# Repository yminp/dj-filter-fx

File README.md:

# dj-filter-fx
A voltage-controlled DJ filter unit with LFO-like envelope function

## Disclaimer
This design has not yet been validated with a physical prototype. The schematic has been reviewed and analyzed, but practical issues may still be discovered during assembly and testing. A prototype is planned to be built and tested soon.

Anyone building the current revision should treat it as an experimental, pre-prototype design rather than a fully validated production circuit.

## Description
This project is a standalone analog filter effects unit intended primarily for DJ use.

The motivation came from the relative lack of dedicated standalone filter FX units for DJs. Filter effects are built into most modern DJ mixers, but older analog mixers may not provide an integrated filter effect. In those cases, applying a filter generally requires an external effects processor connected through the mixer's send/return path. The goal of this project is therefore to provide a dedicated external filter effect that can be used with such mixers while retaining an analog signal path.

Another major purpose of the project was educational. I wanted to explore the use of operational transconductance amplifiers (OTAs), particularly the LM13700, as voltage-controlled amplifiers (VCAs). In this design, VCAs are used inside a state-variable filter to provide voltage control of both the filter's center frequency and resonance Q. This required treating the OTA not merely as a conventional variable-resistance element, but as a controllable transconductance stage whose gain can be incorporated into the state-variable filter equations.

The project consequently combines several topics that I wanted to study in a practical audio circuit:

- voltage-controlled state-variable filters;
- LM13700 OTA/VCA design;
- voltage control of cutoff frequency and resonance;
- envelope-controlled filtering;
- LFO-based filter modulation;
- analog switching and filter-mode selection;
- balanced audio input and output interfacing;
- gain structure and headroom for professional/DJ audio levels (accepting input up to +26dBu, balanced).

The design is intended both as a usable DJ effects unit and as an experimental platform for learning analog filter and voltage-controlled amplifier design.

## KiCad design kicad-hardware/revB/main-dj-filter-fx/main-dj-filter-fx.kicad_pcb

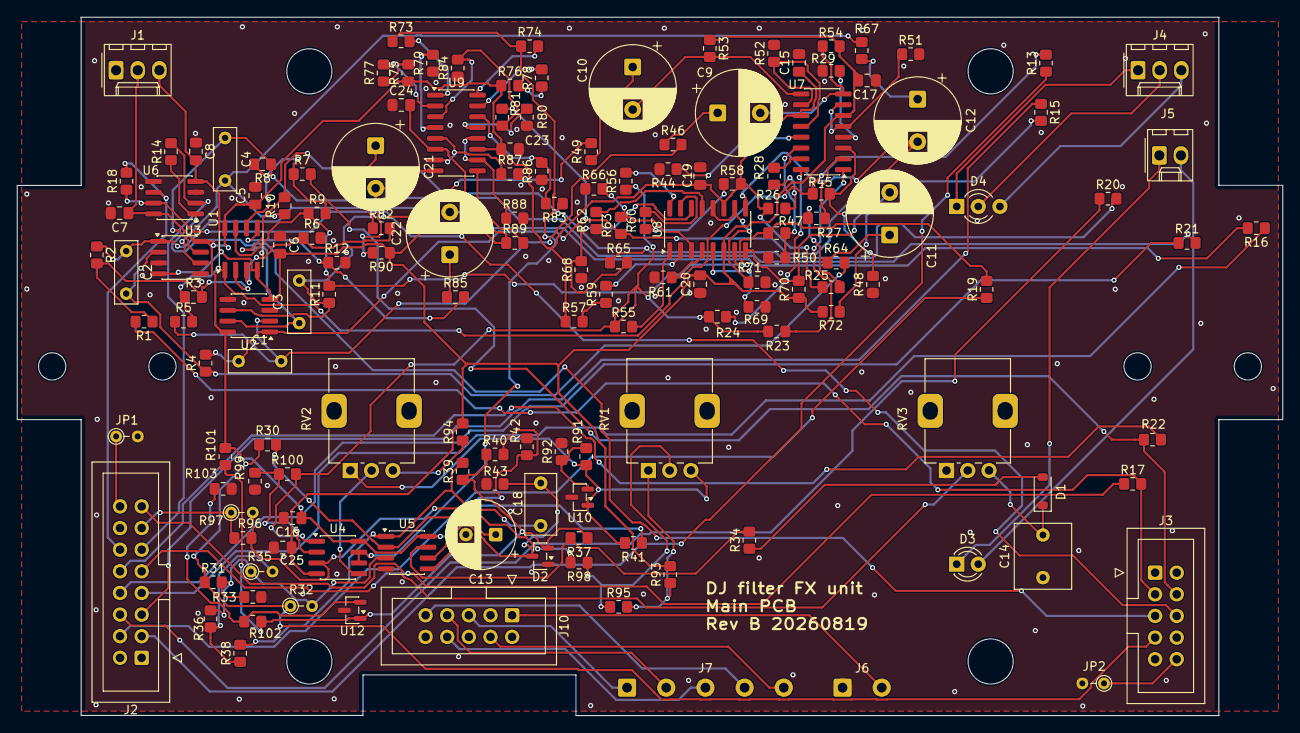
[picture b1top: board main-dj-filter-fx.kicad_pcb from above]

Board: 2 copper layers, 148.6 x 82.0 mm, 156 parts (0 on the bottom side), 116 nets.

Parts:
C1, C2, C3, C4: 2.2n, 1%; C_Rect_L7.2mm_W2.5mm_P5.00mm
C5, C6, C7, C8, C15, C16, C17, C19, C20, C23, C24, C25: 100n; C_0805_2012Metric_Pad1.18x1.45mm_HandSolder
C9, C10, C11, C12, C21, C22: 22u, NP; CP_Radial_D10.0mm_P5.00mm
C13: 10u, NP; CP_Radial_D8.0mm_P3.50mm
C14: 1u, film; C_Rect_L7.5mm_W6.5mm_P5.00mm
C18: 100n, film; C_Rect_L7.0mm_W3.5mm_P5.00mm
D1: MMSD4148; D_SOD-123
D2: BAT54S; SOT-23
D3: RED; LED_D3.0mm
D4: RED_GREEN; LED_D3.0mm-3
J1: PW_CONN; Molex_KK-254_AE-6410-03A_1x03_P2.54mm_Vertical
J2: SW_CONN; IDC-Header_2x08_P2.54mm_Vertical
J3: CONN_SIG; IDC-Header_2x05_P2.54mm_Vertical
J4: LED2color_CONN; Molex_KK-254_AE-6410-03A_1x03_P2.54mm_Vertical
J5: LED; Molex_KK-254_AE-6410-02A_1x02_P2.54mm_Vertical
J6: Conn_01x02_Socket; SolderWire-0.5sqmm_1x02_P4.6mm_D0.9mm_OD2.1mm
J7: Conn_01x05_Socket; SolderWire-0.5sqmm_1x05_P4.6mm_D0.9mm_OD2.1mm
J10: PHYSW_CONN; IDC-Header_2x05_P2.54mm_Vertical
JP1, JP2: Jumper_2_Small_Open; R_Axial_DIN0204_L3.6mm_D1.6mm_P2.54mm_Vertical
R1, R2, R3, R7, R8, R9, R37, R39, R53, R54, R70, R72, R89, R90: 4K7; R_0805_2012Metric_Pad1.20x1.40mm_HandSolder
R4, R5, R10, R11: 22M; R_0805_2012Metric_Pad1.20x1.40mm_HandSolder
R6, R12, R13, R14, R15, R16, R17, R18, R19, R20, R21, R22, R42, R102, R103: 10K; R_0805_2012Metric_Pad1.20x1.40mm_HandSolder
R23, R24, R55, R56, R73, R74: 27K; R_0805_2012Metric_Pad1.20x1.40mm_HandSolder
R25, R26, R46, R49, R57, R58, R64, R67, R75, R76, R92, R101: 2K2; R_0805_2012Metric_Pad1.20x1.40mm_HandSolder
R27, R28, R59, R60, R77, R78: 12K; R_0805_2012Metric_Pad1.20x1.40mm_HandSolder
R29, R44, R48, R50, R61, R62, R66, R68, R79, R80, R84, R86: 470; R_0805_2012Metric_Pad1.20x1.40mm_HandSolder
R30, R98: 220K; R_0805_2012Metric_Pad1.20x1.40mm_HandSolder
R31: 47K; R_0805_2012Metric_Pad1.20x1.40mm_HandSolder
R32: 100K, TH; R_Axial_DIN0204_L3.6mm_D1.6mm_P2.54mm_Vertical
R33, R99: 100K; R_0805_2012Metric_Pad1.20x1.40mm_HandSolder
R34: 1K; R_0805_2012Metric_Pad1.20x1.40mm_HandSolder
R35: 1M, TH; R_Axial_DIN0204_L3.6mm_D1.6mm_P2.54mm_Vertical
R36: 10R; R_0805_2012Metric_Pad1.20x1.40mm_HandSolder
R38: 1M; R_0805_2012Metric_Pad1.20x1.40mm_HandSolder
R40, R51, R52, R69, R71: 39K; R_0805_2012Metric_Pad1.20x1.40mm_HandSolder
R41: 680R; R_0805_2012Metric_Pad1.20x1.40mm_HandSolder
R43, R87, R88, R100: 68K; R_0805_2012Metric_Pad1.20x1.40mm_HandSolder
R45, R47, R63, R65, R81, R83: 150K; R_0805_2012Metric_Pad1.20x1.40mm_HandSolder
R82, R85: 3K3; R_0805_2012Metric_Pad1.20x1.40mm_HandSolder
R91: 8K2; R_0805_2012Metric_Pad1.20x1.40mm_HandSolder
R93: 5K6; R_0805_2012Metric_Pad1.20x1.40mm_HandSolder
R94: 18K; R_0805_2012Metric_Pad1.20x1.40mm_HandSolder
R95: 33K; R_0805_2012Metric_Pad1.20x1.40mm_HandSolder
R96: 330K; R_0805_2012Metric_Pad1.20x1.40mm_HandSolder
R97: 680K, TH; R_Axial_DIN0204_L3.6mm_D1.6mm_P2.54mm_Vertical
RV1, RV2, RV3: 100KA; Potentiometer_Alps_RK09K_Single_Vertical
U1, U6: RC4580; SOIC-8_3.9x4.9mm_P1.27mm
U2, U3: TL072; SOIC-8_3.9x4.9mm_P1.27mm
U4: LM358; SOIC-8_3.9x4.9mm_P1.27mm
U5: LM2903; SOIC-8_3.9x4.9mm_P1.27mm
U7, U8, U9: LM13700; SOIC-16_3.9x9.9mm_P1.27mm
U10: TL431; SOT-23
U12: TL431DBZ; SOT-23

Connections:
+15V: C5.1, C7.1, C15.1, C16.1, C19.1, C23.1, J1.2, R25.1, R26.1, R41.1, R57.1, R58.1, R75.1, R76.1, R101.1, U1.8 (V+), U2.8 (V+), U3.8 (V+), U4.8 (V+), U5.8 (V+), U6.8 (V+), U7.11 (V+), U8.11 (V+), U9.11 (V+)
-15V: C6.2, C8.2, C17.2, C20.2, C24.2, C25.2, J1.3, R53.1, R54.1, R70.1, R72.1, R89.1, R90.1, R93.2, R94.2, U1.4 (V-), U2.4 (V-), U3.4 (V-), U4.4 (V-), U6.4 (V-), U7.6 (V-), U8.6 (V-), U9.6 (V-)
/Main/+5V_LOGIC: J6.2, J10.1
/Main/BPF_LOGIC: J7.2, J10.7
/Main/Bypass_LOGIC: J7.4, J10.9
/Main/ENV_LOGIC: J7.5, J10.4
/Main/HPF_LOGIC: J7.1, J10.5
/Main/LPF_LOGIC: J7.3, J10.8
/Main/SVF/BP_L: C1.1, R4.2, R15.2, R63.1, R81.1, U2.1
/Main/SVF/BP_R: C3.1, R10.2, R20.2, R65.1, R83.1, U2.7
/Main/SVF/From-VCA1_L: C1.2, R5.1, R46.2, U2.2 (-)
/Main/SVF/From-VCA1_R: C3.2, R11.1, R49.2, U2.6 (-)
/Main/SVF/From-VCA2_L: C2.2, R4.1, R64.2, U3.2 (-)
/Main/SVF/From-VCA2_R: C4.2, R10.1, R67.2, U3.6 (-)
/Main/SVF/From-VCA3_L: R6.1, R82.2, U1.3 (+)
/Main/SVF/From-VCA3_R: R12.1, R85.2, U1.5 (+)
/Main/SVF/HP_L: R3.1, R5.2, R13.2, R45.1, U1.1
/Main/SVF/HP_R: R9.1, R11.2, R19.2, R47.1, U1.7
/Main/SVF/LP_L: C2.1, R2.1, R16.2, U3.1
/Main/SVF/LP_R: C4.1, R8.1, R21.2, U3.7
/Main/VCA (K)/VCA-K_CTRL: R23.1, R24.1, R55.1, R56.1, R100.2, U4.1
/Main/VCA (Q)/VCA-Q_CTRL: R73.1, R74.1, U4.6 (-), U4.7
/Main/VCA control/+5V_COMP: D2.2 (K), R37.1, R39.1, R40.1, R101.2, R102.1, U12.1 (K)
/Main/VCA control/RECT_AVG: C13.1, R30.2, U5.2 (-)
/Main/VCA control/RECT_FAST: R31.2, R32.2, R33.1, R35.1, R36.1, U5.3 (+)
BP_TMUX_L: J2.5, R15.1
BP_TMUX_R: J2.6, R20.1
Bypass_TMUX_L: J2.9, R17.1
Bypass_TMUX_R: J2.10, R22.1
ENV_DEPTH: J2.15, RV3.2
ENV_OUT: J2.13, R96.1, R97.1
GNDA: C5.2, C6.1, C7.2, C8.1, C13.2, C14.1, C15.2, C16.2, C17.1, C19.2, C20.1, C23.2, C24.1, C25.1, D2.1 (A), J1.1, J6.1, J10.10, JP1.2 (B), JP2.2 (B), R6.2, R12.2, R29.1, R33.2, R42.2, R43.2, R44.1, R48.1, R50.1, R51.2, R52.2, R61.1, R62.1, R66.1, R68.1, R69.2, R71.2, R79.1, R80.1, R84.1, R86.1, R87.2, R88.2, R92.2, R99.1, R103.2, RV3.1, U2.3 (+), U2.5 (+), U3.3 (+), U3.5 (+), U5.4 (V-), U6.3 (+), U6.5 (+), U10.3 (A), U12.3 (A)
HP_TMUX_L: J2.3, R13.1
HP_TMUX_R: J2.4, R19.1
LP_TMUX_L: J2.7, R16.1
LP_TMUX_R: J2.8, R21.1
unnamed: C9.1, R46.1
unnamed: C9.2, R54.2, U7.8
unnamed: C10.1, R49.1
unnamed: C10.2, R53.2, U7.9
unnamed: C11.1, R64.1
unnamed: C11.2, R70.2, U8.8
unnamed: C12.1, R67.1
unnamed: C12.2, R72.2, U8.9
unnamed: C18.2, R38.2, R39.2, U5.1
unnamed: C21.1, R82.1
unnamed: C21.2, R90.2, U9.8
unnamed: C22.1, R85.1
unnamed: C22.2, R89.2, U9.9
unnamed: D1.2 (A), R34.1
unnamed: C14.2, D1.1 (K), RV3.3
unnamed: C18.1, D2.3 (COM), R43.1, U5.5 (+)
unnamed: D3.2 (A), J5.2
unnamed: D3.1 (K), J5.1
unnamed: D4.1 (A1), J4.1
unnamed: D4.3 (A2), J4.3
unnamed: D4.2 (K), J4.2
unnamed: J2.16, JP1.1 (A)
unnamed: J3.10, JP2.1 (A)
unnamed: R23.2, U7.1
unnamed: R24.2, U7.16
unnamed: R25.2, R27.1
unnamed: R26.2, R28.1
unnamed: R34.2, R37.2, U5.7
unnamed: R35.2, R36.2, R38.1
unnamed: R51.1, U7.5, U7.7
unnamed: R52.1, U7.10, U7.12
unnamed: R55.2, U8.1
unnamed: R56.2, U8.16
unnamed: R57.2, R59.1
unnamed: R58.2, R60.1
unnamed: R69.1, U8.5, U8.7
unnamed: R71.1, U8.10, U8.12
unnamed: R73.2, U9.1
unnamed: R74.2, U9.16
unnamed: R75.2, R77.1
unnamed: R76.2, R78.1
unnamed: R87.1, U9.5, U9.7
unnamed: R88.1, U9.10, U9.12
unnamed: R93.1, R95.2, RV1.1
unnamed: R94.1, RV2.3
unnamed: R95.1, R98.1, RV1.2
unnamed: R1.1, R2.2, R3.2, U1.2 (-)
unnamed: R7.1, R8.2, R9.2, U1.6 (-)
unnamed: R96.2, R97.2, R98.2, U4.3 (+)
unnamed: R99.2, R100.1, U4.2 (-)
unnamed: RV2.2, U4.5 (+)
unnamed: R40.2, R42.1, U5.6 (-)
unnamed: R47.2, R50.2, U7.14 (+)
unnamed: R44.2, U7.13 (-)
unnamed: R28.2, U7.15 (DIODE_BIAS)
unnamed: R45.2, R48.2, U7.3 (+)
unnamed: R29.2, U7.4 (-)
unnamed: R27.2, U7.2 (DIODE_BIAS)
unnamed: R65.2, R68.2, U8.14 (+)
unnamed: R62.2, U8.13 (-)
unnamed: R60.2, U8.15 (DIODE_BIAS)
unnamed: R63.2, R66.2, U8.3 (+)
unnamed: R61.2, U8.4 (-)
unnamed: R59.2, U8.2 (DIODE_BIAS)
unnamed: R83.2, R86.2, U9.14 (+)
unnamed: R80.2, U9.13 (-)
unnamed: R78.2, U9.15 (DIODE_BIAS)
unnamed: R81.2, R84.2, U9.3 (+)
unnamed: R79.2, U9.4 (-)
unnamed: R77.2, U9.2 (DIODE_BIAS)
unnamed: R41.2, R91.1, RV1.3, RV2.1, U10.1 (K)
unnamed: R91.2, R92.1, U10.2 (REF)
unnamed: R102.2, R103.1, U12.2 (REF)
RECT: J3.7, R30.1, R31.1, R32.1
SUM_OUT_L: J3.5, R14.1, U6.1
SUM_OUT_R: J3.6, R18.1, U6.7
SUM_TMUX_L: J2.11, R14.2, U6.2 (-)
SUM_TMUX_R: J2.12, R18.2, U6.6 (-)
SVF_IN_L: J3.3, R1.2, R17.2
SVF_IN_R: J3.4, R7.2, R22.2

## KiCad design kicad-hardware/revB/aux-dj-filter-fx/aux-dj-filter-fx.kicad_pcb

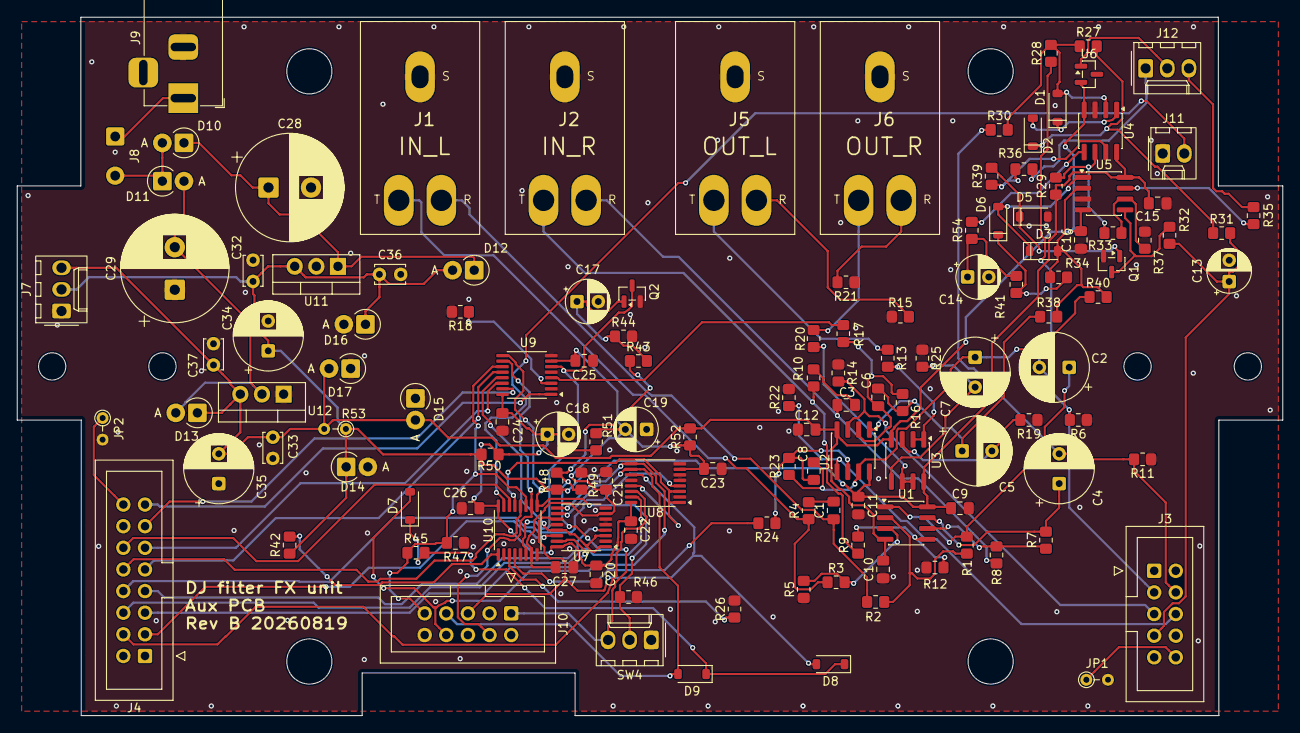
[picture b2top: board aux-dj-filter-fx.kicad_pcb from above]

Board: 2 copper layers, 148.6 x 82.0 mm, 134 parts (0 on the bottom side), 87 nets.

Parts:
C1, C3: 220p, NP0; C_0805_2012Metric_Pad1.18x1.45mm_HandSolder
C2, C4, C5, C7: 22u, 25V; CP_Radial_D8.0mm_P3.50mm
C6, C8: 47p, NP0; C_0805_2012Metric_Pad1.18x1.45mm_HandSolder
C9, C10, C11, C12, C15, C16, C20, C21, C22, C23, C24, C25, C26, C27: 100n; C_0805_2012Metric_Pad1.18x1.45mm_HandSolder
C13, C14: 1u, 25V; CP_Radial_D5.0mm_P2.50mm
C17, C18, C19: 10u, 25V; CP_Radial_D5.0mm_P2.50mm
C28, C29: 1000u, 35V; CP_Radial_D12.5mm_P5.00mm
C32: 100n; C_Disc_D3.4mm_W2.1mm_P2.50mm
C33: 1u; C_Disc_D3.4mm_W2.1mm_P2.50mm
C34, C35: 220u, 25V; CP_Radial_D8.0mm_P3.50mm
C36, C37: 1u, TH; C_Disc_D3.4mm_W2.1mm_P2.50mm
D1, D2, D3, D5, D6: MMSD4148; D_SOD-123_K-mark
D7, D8, D9: MMSD4148; D_SOD-123
D10, D11, D12, D13, D14, D15: 1N4002; D_DO-41_SOD81_P2.54mm_Vertical_AnodeUp
D16, D17: 18V, 1W, TH; D_DO-41_SOD81_P2.54mm_Vertical_AnodeUp
J1: IN_L; Generic_6.35mm_TRS_3pins
J2: IN_R; Generic_6.35mm_TRS_3pins
J3: CONN_SIG; IDC-Header_2x05_P2.54mm_Vertical
J4: SW_CONN; IDC-Header_2x08_P2.54mm_Vertical
J5: OUT_L; Generic_6.35mm_TRS_3pins
J6: OUT_R; Generic_6.35mm_TRS_3pins
J7: PW_CONN; Molex_KK-254_AE-6410-03A_1x03_P2.54mm_Vertical
J8: FUSE_SW; SolderWire-0.5sqmm_1x02_P4.6mm_D0.9mm_OD2.1mm
J9: 16VAC; BarrelJack_Horizontal
J10: PHYSW_CONN; IDC-Header_2x05_P2.54mm_Vertical
J11: Conn_01x02_Pin; Molex_KK-254_AE-6410-02A_1x02_P2.54mm_Vertical
J12: Conn_01x03_Pin; Molex_KK-254_AE-6410-03A_1x03_P2.54mm_Vertical
JP1, JP2: Jumper_2_Small_Open; R_Axial_DIN0204_L3.6mm_D1.6mm_P2.54mm_Vertical
Q1, Q2: MMBT3904; SOT-23
R1, R5, R7, R12, R33, R49: 4K7; R_0805_2012Metric_Pad1.20x1.40mm_HandSolder
R2, R3, R8, R9, R42: 15K; R_0805_2012Metric_Pad1.20x1.40mm_HandSolder
R4, R10, R13, R15, R20, R21: 100R; R_0805_2012Metric_Pad1.20x1.40mm_HandSolder
R6, R11, R14, R19, R22, R25, R35, R36, R44, R48: 10K; R_0805_2012Metric_Pad1.20x1.40mm_HandSolder
R16, R23, R29: 6K8; R_0805_2012Metric_Pad1.20x1.40mm_HandSolder
R17, R24: 3K3; R_0805_2012Metric_Pad1.20x1.40mm_HandSolder
R18, R26, R28, R30, R47: 47K; R_0805_2012Metric_Pad1.20x1.40mm_HandSolder
R27: 68K; R_0805_2012Metric_Pad1.20x1.40mm_HandSolder
R31, R41: 1K8; R_0805_2012Metric_Pad1.20x1.40mm_HandSolder
R32, R54: 470K; R_0805_2012Metric_Pad1.20x1.40mm_HandSolder
R34: 51K; R_0805_2012Metric_Pad1.20x1.40mm_HandSolder
R37: 220R; R_0805_2012Metric_Pad1.20x1.40mm_HandSolder
R38, R40: 100K; R_0805_2012Metric_Pad1.20x1.40mm_HandSolder
R39, R43: 39K; R_0805_2012Metric_Pad1.20x1.40mm_HandSolder
R45, R46: 22K; R_0805_2012Metric_Pad1.20x1.40mm_HandSolder
R50, R52: 5K1; R_0805_2012Metric_Pad1.20x1.40mm_HandSolder
R51: 33K; R_0805_2012Metric_Pad1.20x1.40mm_HandSolder
R53: 1M, TH; R_Axial_DIN0204_L3.6mm_D1.6mm_P2.54mm_Vertical
SW4: ATTN_SW; Molex_KK-254_AE-6410-03A_1x03_P2.54mm_Vertical
U1, U2, U3: RC4580; SOIC-8_3.9x4.9mm_P1.27mm
U4, U5: TL072; SOIC-8_3.9x4.9mm_P1.27mm
U6: LM4040DBZ-2.0; SOT-23
U7, U8, U9, U10: TMUX4053; TSSOP-16_4.4x5mm_P0.65mm
U11: L7815; TO-220-3_Vertical
U12: L7915; TO-220-3_Vertical

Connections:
+11.5V: C18.1, C20.1, C22.1, C24.1, C26.1, R50.2, R51.1, U7.16 (VDD), U8.16 (VDD), U9.16 (VDD), U10.16 (VDD)
+15V: C9.1, C11.1, C15.1, C32.1, C34.1, C36.1, D12.2 (A), D14.1 (K), D16.1 (K), J7.2, R29.1, R42.1, R48.1, R50.1, R53.1, U1.8 (V+), U2.8 (V+), U3.8 (V+), U4.8 (V+), U5.8 (V+), U11.3 (OUT)
-11.5V: C19.2, C21.2, C23.2, C25.2, C27.2, R51.2, R52.1, U7.7 (VEE), U8.7 (VEE), U9.7 (VEE), U10.7 (VEE)
-15V: C10.2, C12.2, C16.2, C33.2, C35.2, C37.2, D13.1 (K), D15.2 (A), D17.2 (A), J7.3, R52.2, R53.2, U1.4 (V-), U2.4 (V-), U3.4 (V-), U4.4 (V-), U5.4 (V-), U6.2 (A), U12.3 (VO)
/Auxiliary/IO/ATTN_L: R17.2, U9.4 (C)
/Auxiliary/IO/ATTN_Ly: R18.1, U9.3 (C1)
/Auxiliary/IO/ATTN_R: R24.2, U10.4 (C)
/Auxiliary/IO/ATTN_Ry: R26.1, U10.3 (C1)
/Auxiliary/IO/IN_L_C: C1.1, J1.R, R2.1
/Auxiliary/IO/IN_L_H: J1.T, R3.1, R4.1
/Auxiliary/IO/IN_R_C: C3.1, J2.R, R8.1
/Auxiliary/IO/IN_R_H: J2.T, R9.1, R10.1
/Auxiliary/IO/LED_L_POST: C5.1, C6.2, R16.1, R38.1, U2.1
/Auxiliary/IO/LED_R_POST: C7.1, C8.2, R23.1, R40.1, U2.7
/Auxiliary/IO/OUT_L_C: J5.R, R15.2
/Auxiliary/IO/OUT_L_H: J5.T, R13.1
/Auxiliary/IO/OUT_R_C: J6.R, R21.2
/Auxiliary/IO/OUT_R_H: J6.T, R20.1
/Auxiliary/LFO_LED: J11.2, U10.15 (B)
/Auxiliary/LFO_LED_I: R42.2, U10.1 (B1)
/Auxiliary/Power supply/PS_AC1: D10.2 (A), D11.1 (K), J8.2
/Auxiliary/Swtich/+5V_LOGIC: J10.1, R43.1, R48.2, R49.1, SW4.3 (C)
/Auxiliary/Swtich/ATTN_LOGIC: R46.2, SW4.2 (B), U9.9 (S3), U10.9 (S3)
/Auxiliary/Swtich/BPF_LOGIC: D9.2 (A), J10.7, U7.10 (S2), U8.10 (S2)
/Auxiliary/Swtich/Bypass_LOGIC: J10.9, R45.1, R47.2, U9.11 (S1), U10.11 (S1)
/Auxiliary/Swtich/Bypass_override: D7.1 (K), D8.1 (K), D9.1 (K), R45.2
/Auxiliary/Swtich/ENV_LOGIC: J10.4, U9.10 (S2), U10.10 (S2)
/Auxiliary/Swtich/FILTER-BUS_L: U7.1 (B1), U7.3 (C1), U7.13 (A1), U9.13 (A1)
/Auxiliary/Swtich/FILTER-BUS_R: U8.1 (B1), U8.3 (C1), U8.13 (A1), U10.13 (A1)
/Auxiliary/Swtich/HPF_LOGIC: D8.2 (A), J10.5, U7.11 (S1), U8.11 (S1)
/Auxiliary/Swtich/LPF_LOGIC: D7.2 (A), J10.8, U7.9 (S3), U8.9 (S3)
/Auxiliary/Swtich/STARTUP: Q2.3 (C), U9.6 (INH), U10.6 (INH)
BP_TMUX_L: J4.5, U7.15 (B)
BP_TMUX_R: J4.6, U8.15 (B)
Bypass_TMUX_L: J4.9, U9.12 (A0)
Bypass_TMUX_R: J4.10, U10.12 (A0)
ENV_DEPTH: J4.15, U9.1 (B1)
ENV_OUT: J4.13, U9.15 (B)
GNDA: C9.2, C10.1, C11.2, C12.1, C13.2, C14.2, C15.2, C16.1, C17.2, C18.2, C19.1, C20.2, C21.1, C22.2, C23.1, C24.2, C25.1, C26.2, C27.1, C28.2, C29.1, C32.2, C33.1, C34.2, C35.1, C36.2, C37.1, D5.2 (A), D14.2 (A), D15.1 (K), D16.2 (A), D17.1 (K), J1.S, J2.S, J5.S, J6.S, J7.1, J9.2, J10.10, J11.1, JP1.2 (B), JP2.2 (B), Q1.2 (E), Q2.2 (E), R5.1, R6.1, R11.1, R12.1, R14.1, R15.1, R18.2, R19.1, R21.1, R22.1, R25.1, R26.2, R37.2, R44.2, R46.1, R47.1, R49.2, SW4.1 (A), U4.3 (+), U5.3 (+), U7.2 (B0), U7.5 (C0), U7.6 (INH), U7.8 (VSS), U7.12 (A0), U8.2 (B0), U8.5 (C0), U8.6 (INH), U8.8 (VSS), U8.12 (A0), U9.2 (B0), U9.5 (C0), U9.8 (VSS), U10.5 (C0), U10.8 (VSS), U11.2 (GND), U12.1 (GND)
HP_TMUX_L: J4.3, U7.14 (A)
HP_TMUX_R: J4.4, U8.14 (A)
LP_TMUX_L: J4.7, U7.4 (C)
LP_TMUX_R: J4.8, U8.4 (C)
unnamed: C1.2, R4.2
unnamed: C2.1, R1.2, U1.1
unnamed: C3.2, R10.2
unnamed: C4.1, R7.2, U1.7
unnamed: C14.1, R41.2, R54.1
unnamed: D1.2 (A), R27.1, R28.2, R30.2, U4.2 (-)
unnamed: D1.1 (K), D2.2 (A), U4.1
unnamed: D2.1 (K), R27.2, R31.1
unnamed: D3.2 (A), R34.1, R38.2, R40.2, U5.2 (-)
unnamed: D3.1 (K), D6.2 (A), U5.1
unnamed: D5.1 (K), Q1.1 (B), R39.2
unnamed: D6.1 (K), R34.2, R41.1
unnamed: C28.1, D10.1 (K), D12.1 (K), U11.1 (IN)
unnamed: C29.2, D11.2 (A), D13.2 (A), U12.2 (VI)
unnamed: J3.10, JP1.1 (A)
unnamed: J4.16, JP2.1 (A)
unnamed: J8.1, J9.1
unnamed: J12.1, R36.2
unnamed: J12.2, U6.1 (K)
unnamed: J12.3, R35.2
unnamed: Q1.3 (C), R32.2, U5.5 (+)
unnamed: C17.1, Q2.1 (B), R43.2, R44.1
unnamed: R35.1, U5.7
unnamed: R36.1, R39.1, U4.7
unnamed: R3.2, R5.2, U1.3 (+)
unnamed: R1.1, R2.2, U1.2 (-)
unnamed: R9.2, R12.2, U1.5 (+)
unnamed: R7.1, R8.2, U1.6 (-)
unnamed: C6.1, R16.2, R17.1, U2.2 (-)
unnamed: C8.1, R23.2, R24.1, U2.6 (-)
unnamed: C5.2, R19.2, U3.3 (+)
unnamed: R13.2, U3.1, U3.2 (-)
unnamed: C7.2, R25.2, U3.5 (+)
unnamed: R20.2, U3.6 (-), U3.7
unnamed: R54.2, U4.5 (+)
unnamed: R29.2, R33.1, U4.6 (-)
unnamed: R33.2, R37.1, U5.6 (-)
RECT: C13.1, J3.7, R31.2, R32.1
SUM_OUT_L: J3.5, R14.2, U2.3 (+)
SUM_OUT_R: J3.6, R22.2, U2.5 (+)
SUM_TMUX_L: J4.11, U9.14 (A)
SUM_TMUX_R: J4.12, U10.14 (A)
SVF_IN_L: C2.2, J3.3, R6.2, R28.1
SVF_IN_R: C4.2, J3.4, R11.2, R30.1
